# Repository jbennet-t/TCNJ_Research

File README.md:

# TCNJ_Research
Research notes, code, and PCBs created for research projects and development during my time at multiple labs. Check out the wiki for more info!

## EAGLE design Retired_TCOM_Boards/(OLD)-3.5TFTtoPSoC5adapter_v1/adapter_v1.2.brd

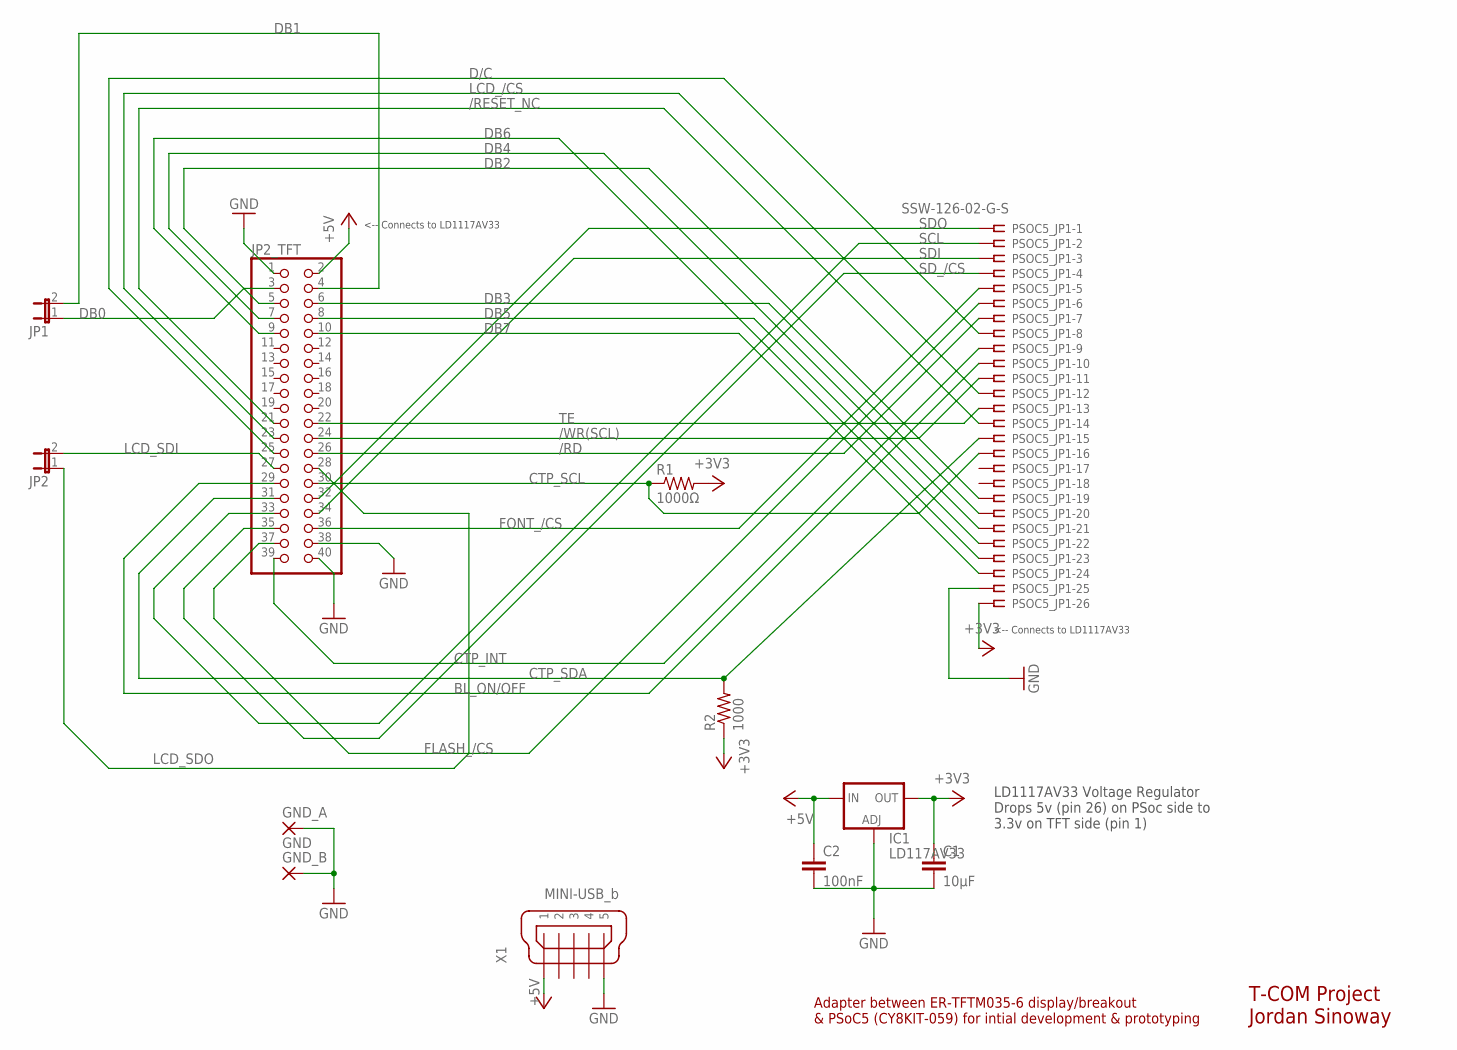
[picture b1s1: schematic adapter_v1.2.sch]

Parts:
C1: 10μF; C2.5-2
C2: 100nF; C2.5-2
GND_A: GND; SMD2,54-5,08
GND_B: SMD5; SMD2,54-5,08
IC1: LD117AV33; TO220L1
JP1, JP2: JP1E; JP1
JP2_TFT: PINHD-2X20; 2X20
PSOC5_JP1: SSW-126-02-G-S
R1: 1000Ω; 0204/7
R2: 1000; 0204/7
X1: MINI-USB_b; 32005-601

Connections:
+3V3: C1.1, IC1.2 (OUT), PSOC5_JP1.26, R1.2, R2.1
+5V: C2.1, IC1.3 (IN), JP2_TFT.2, X1.1
/RD: JP2_TFT.26, PSOC5_JP1.7
/RESET_NC: JP2_TFT.21, PSOC5_JP1.14
/WR(SCL): JP2_TFT.24, PSOC5_JP1.11
BL_ON/OFF: JP2_TFT.29, PSOC5_JP1.10
CTP_INT: JP2_TFT.39, PSOC5_JP1.9
CTP_SCL: JP2_TFT.30, PSOC5_JP1.16, R1.1
CTP_SDA: JP2_TFT.31, PSOC5_JP1.15, R2.2
D/C: JP2_TFT.25, PSOC5_JP1.8
DB0: JP1.1, JP2_TFT.3
DB1: JP1.2, JP2_TFT.4
DB2: JP2_TFT.5, PSOC5_JP1.19
DB3: JP2_TFT.6, PSOC5_JP1.20
DB4: JP2_TFT.7, PSOC5_JP1.21
DB5: JP2_TFT.8, PSOC5_JP1.22
DB6: JP2_TFT.9, PSOC5_JP1.23
DB7: JP2_TFT.10, PSOC5_JP1.24
FLASH_/CS: JP2_TFT.37, PSOC5_JP1.6
FONT_/CS: JP2_TFT.36, PSOC5_JP1.5
GND: C1.2, C2.2, GND_A.1, GND_B.1, IC1.1 (ADJ), JP2_TFT.1, JP2_TFT.38, JP2_TFT.40, PSOC5_JP1.25, X1.5
LCD_/CS: JP2_TFT.23, PSOC5_JP1.12
LCD_SDI: JP2.2, JP2_TFT.27
LCD_SDO: JP2.1, JP2_TFT.28
SCL: JP2_TFT.33, PSOC5_JP1.2
SDI: JP2_TFT.34, PSOC5_JP1.3
SDO: JP2_TFT.32, PSOC5_JP1.1
SD_/CS: JP2_TFT.35, PSOC5_JP1.4
TE: JP2_TFT.22, PSOC5_JP1.13

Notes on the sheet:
LD1117AV33 Voltage Regulator Drops 5v (pin 26) on PSoc side to 3.3v on TFT side (pin 1)
<-- Connects to LD1117AV33
T-COM Project Jordan Sinoway
Adapter between ER-TFTM035-6 display/breakout & PSoC5 (CY8KIT-059) for intial development & prototyping

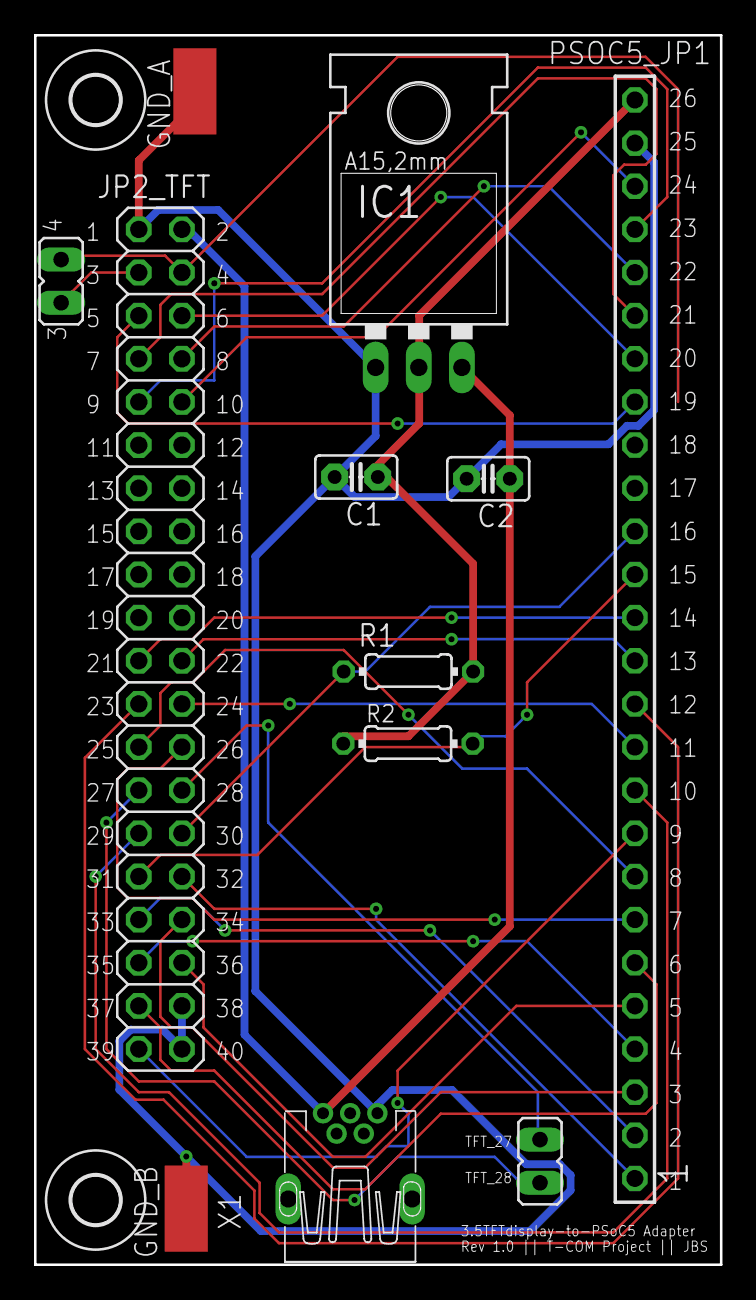
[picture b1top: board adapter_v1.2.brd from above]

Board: 2 copper layers, 40.4 x 72.4 mm, 14 parts (0 on the bottom side), 29 nets.

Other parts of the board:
U$1, U$2: 2,8

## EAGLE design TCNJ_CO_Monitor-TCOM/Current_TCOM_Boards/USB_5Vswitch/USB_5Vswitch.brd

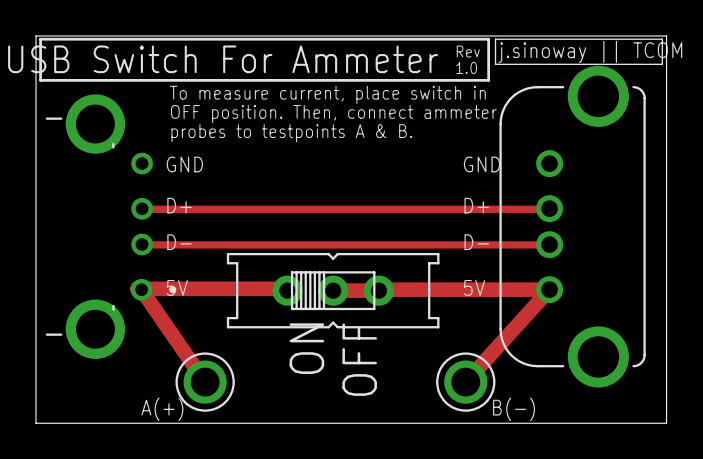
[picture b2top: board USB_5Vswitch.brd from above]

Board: 2 copper layers, 35.0 x 21.5 mm, 5 parts (0 on the bottom side), 5 nets.

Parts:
A(+): 5013; TESTPOINT_5013
B(-): 5013; TESTPOINT_5013
J1: USB-A-S-X-X-VT
J2: 1-1734028-12; TE_1-1734028-2
S1: EG1218

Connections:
+5V: B(-).1, J1.1, S1.P, S1.S
D+: J1.3, J2.3
D-: J1.2, J2.2
GND: J1.4, J1.G1, J1.G2, J2.4, J2.S1, J2.S2
unnamed: A(+).1, J2.1, S1.O

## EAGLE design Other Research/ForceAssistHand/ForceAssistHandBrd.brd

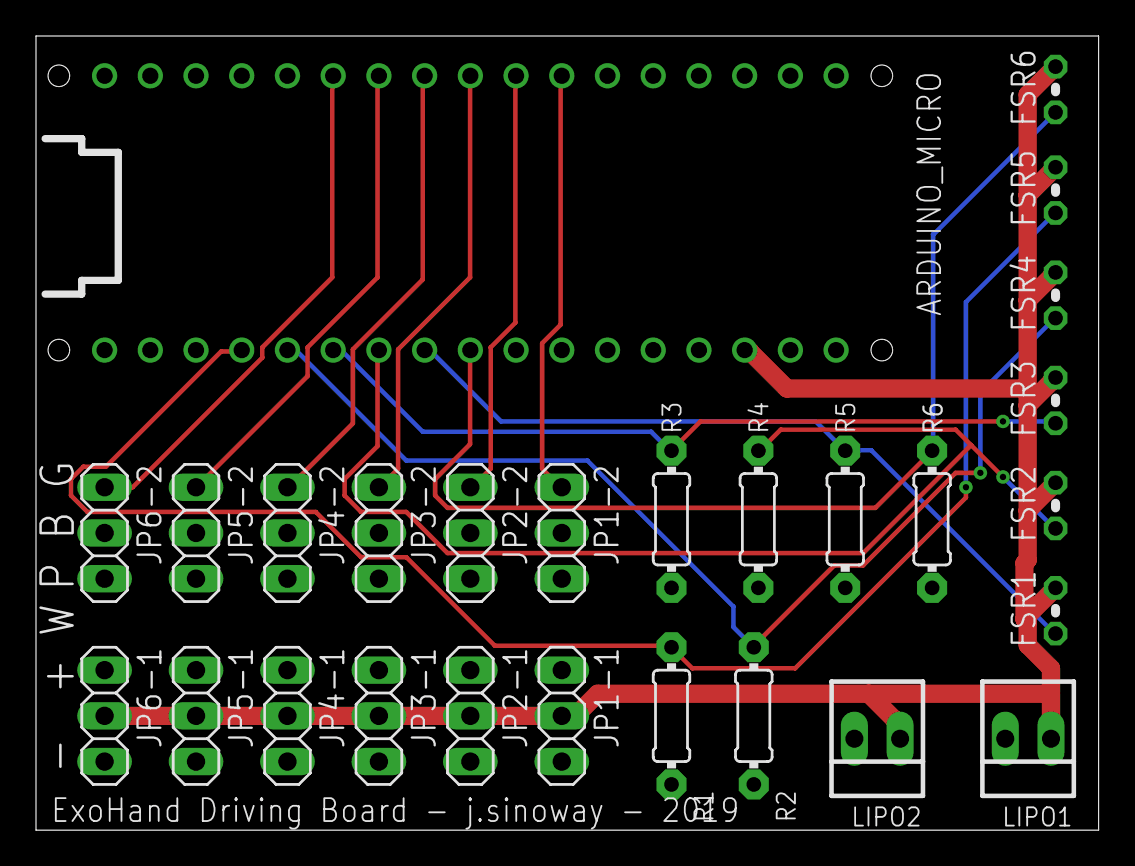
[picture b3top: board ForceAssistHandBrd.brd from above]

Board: 2 copper layers, 59.0 x 44.1 mm, 27 parts (0 on the bottom side), 14 nets.

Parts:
ARDUINO_MICRO: ARDUINO_MICROFOOTPRINT; ARDUINO-MICRO
FSR1, FSR2, FSR3, FSR4, FSR5, FSR6: 0204V
JP1-1, JP1-2, JP2-1, JP2-2, JP3-1, JP3-2, JP4-1, JP4-2, JP5-1, JP5-2, JP6-1, JP6-2: 1X03
LIPO1, LIPO2: 22-23-2021
R1, R2, R3, R4, R5, R6: 1k; 0204/7

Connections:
GND: ARDUINO_MICRO.GND, ARDUINO_MICRO.GND1, JP1-1.3, JP2-1.3, JP3-1.3, JP4-1.3, JP5-1.3, JP6-1.3, LIPO1.2, LIPO2.2, R1.2, R2.2, R3.2, R4.2, R5.2, R6.2
unnamed: ARDUINO_MICRO.D2, JP1-2.1
unnamed: ARDUINO_MICRO.D3, JP2-2.1
unnamed: ARDUINO_MICRO.D4, JP3-2.1
unnamed: ARDUINO_MICRO.D5, JP4-2.1
unnamed: ARDUINO_MICRO.D6, JP5-2.1
unnamed: ARDUINO_MICRO.A5, FSR6.1, R6.1
unnamed: ARDUINO_MICRO.A3, FSR2.1, R4.1
unnamed: ARDUINO_MICRO.A4, FSR1.1, R5.1
unnamed: ARDUINO_MICRO.A2, FSR3.1, R3.1
unnamed: ARDUINO_MICRO.A1, FSR4.1, R2.1
unnamed: ARDUINO_MICRO.A0, FSR5.1, R1.1
unnamed: ARDUINO_MICRO.D7, JP6-2.1
VCC: ARDUINO_MICRO.VIN, FSR1.2, FSR2.2, FSR3.2, FSR4.2, FSR5.2, FSR6.2, JP1-1.2, JP2-1.2, JP3-1.2, JP4-1.2, JP5-1.2, JP6-1.2, LIPO1.1, LIPO2.1

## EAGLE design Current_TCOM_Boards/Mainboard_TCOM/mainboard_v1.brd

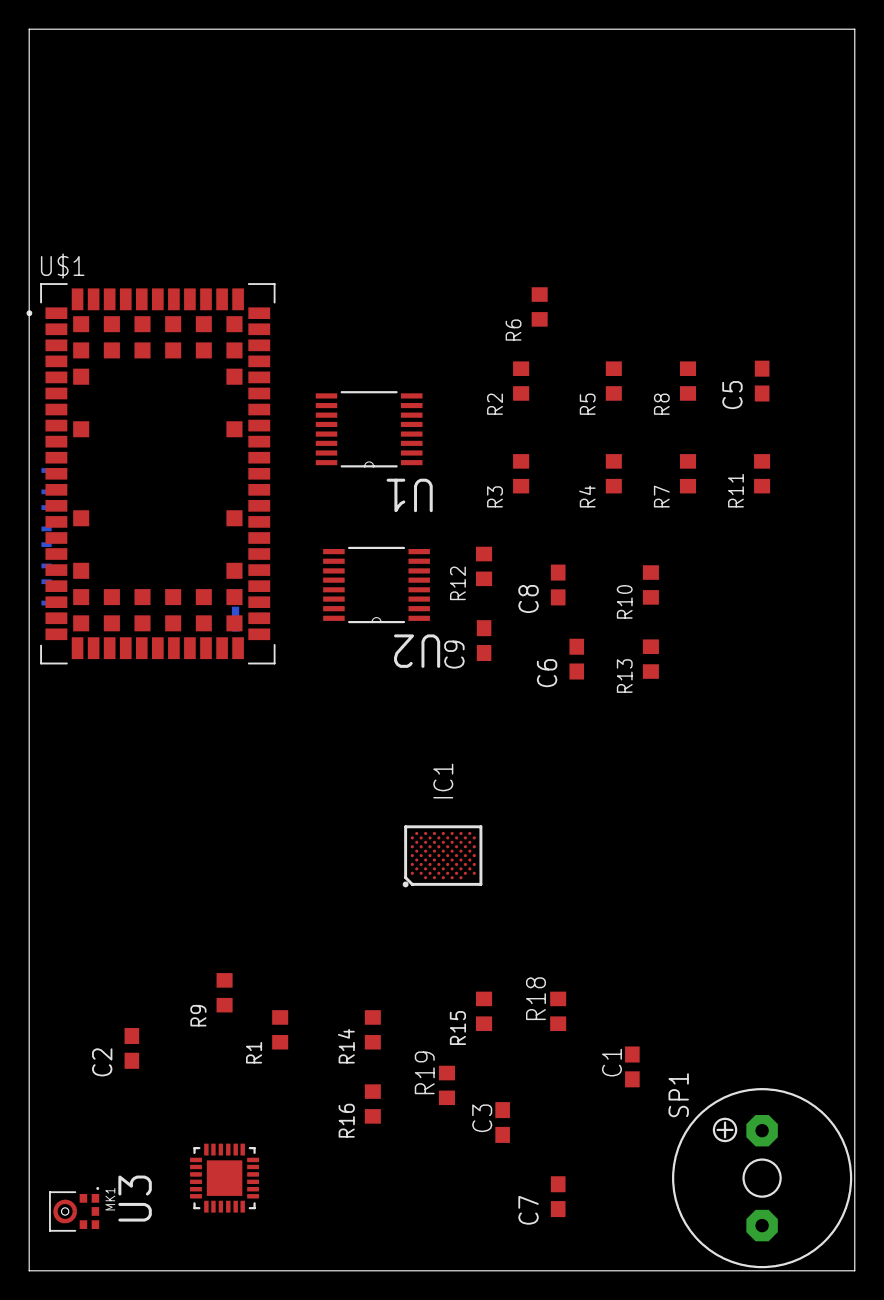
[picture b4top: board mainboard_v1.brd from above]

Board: 4 copper layers, 56.6 x 85.1 mm, 34 parts (1 on the bottom side), 30 nets, no tracks yet.

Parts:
C1: 200pF; C0603
C2, C7: 100nF; C0603
C3: .1uF; C0603
C5, C6, C8, C9: 0.01uF; C0603
IC1: CY8C6247FDI-D32T; BGA80C30P11X15_368X319X47
MK1: SPH0645LM4H-B; MIC_SPH0645LM4H-B
R1, R2, R3, R4, R5, R6, R7, R8, R9, R10, R11, R12, R13, R14, R15, R16, R18: 1k; R0603
R19: 100k; R0603
SIM: 2199337-5; TE_2199337-5
SP1: KSS1201
U1, U2: SN74AVC4T774PWR; SOP65P640X120-16N
U3: TFA9879HN/N1,118; QFN50P260X260X100-25N
U$1: SARA-U260; XCVR_SARA-N200-02B

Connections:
1.8V: C2.1, U3.23
+3V3: C1.1, C3.1, C6.1, C9.1, MK1.5, R3.2, R5.2, R11.2, U1.16, U2.16, U3.7, U3.8
ADSEL1: R15.2, U3.16
ADSEL2: R16.2, U3.4
AUDIO_SDI: MK1.6, R19.2
AUDIO_WS: MK1.1, U3.22
GND: C1.2, C2.2, C3.2, C5.2, C6.2, C7.2, C8.2, C9.2, MK1.3, R1.1, R2.2, R4.2, R6.2, R7.2, R8.2, R9.1, R10.1, R12.2, R13.2, R14.1, R15.1, R16.1, R18.1, R19.1, SIM.C5, SIM.G1, SIM.G2, SIM.G3, SIM.G4, U1.10, U2.10, U3.3, U3.5, U3.11, U3.12, U3.15, U3.24, U3.25
LRCK2: R1.2, U3.19
unnamed: R3.1, U1.1
unnamed: R4.1, U1.2
unnamed: R5.1, U1.7
unnamed: MK1.2, R18.2
unnamed: R6.1, U1.8
unnamed: R7.1, U2.1
unnamed: R11.1, U2.2
unnamed: R12.1, U2.7
unnamed: R8.1, U2.9
unnamed: R13.1, U2.8
unnamed: R10.2, U2.11
unnamed: R2.1, U1.9
SCK2: R9.2, U3.18
SDI2: R14.2, U3.17
SIM_CLK: SIM.C3, U$1.38
SIM_IO: SIM.C7, U$1.39
SIM_RST: SIM.C2, U$1.40
SP+: SP1.+, U3.10
SP-: SP1.-, U3.9
STABA: C7.1, U3.13
VSIM: SIM.C1, U$1.41
V_INT: C5.1, C8.1, U1.15, U2.15

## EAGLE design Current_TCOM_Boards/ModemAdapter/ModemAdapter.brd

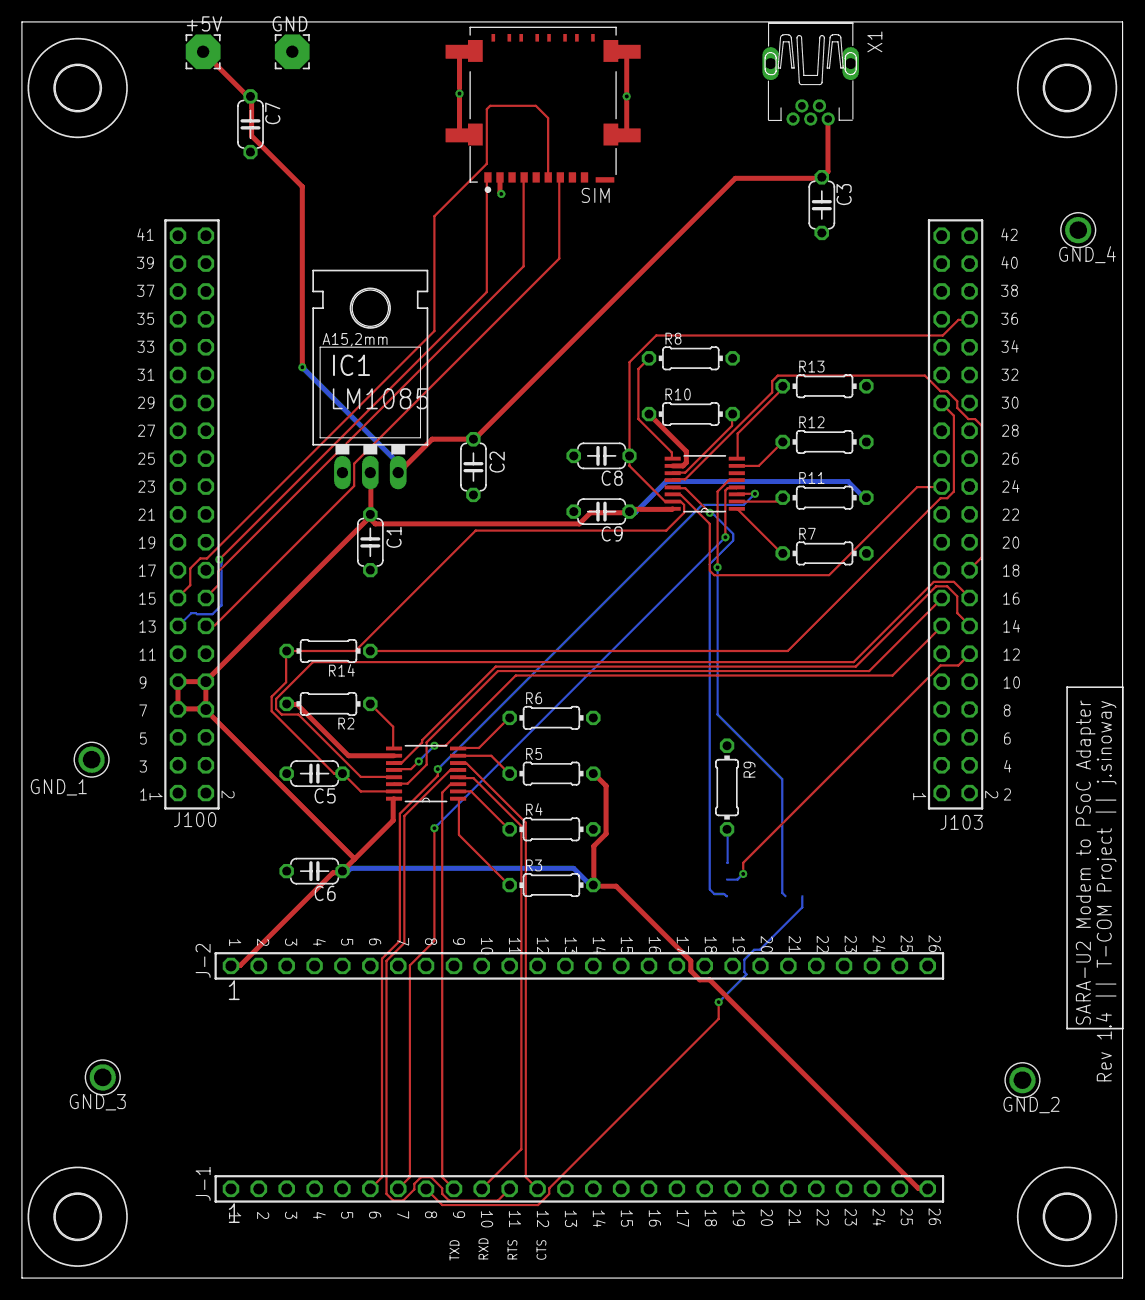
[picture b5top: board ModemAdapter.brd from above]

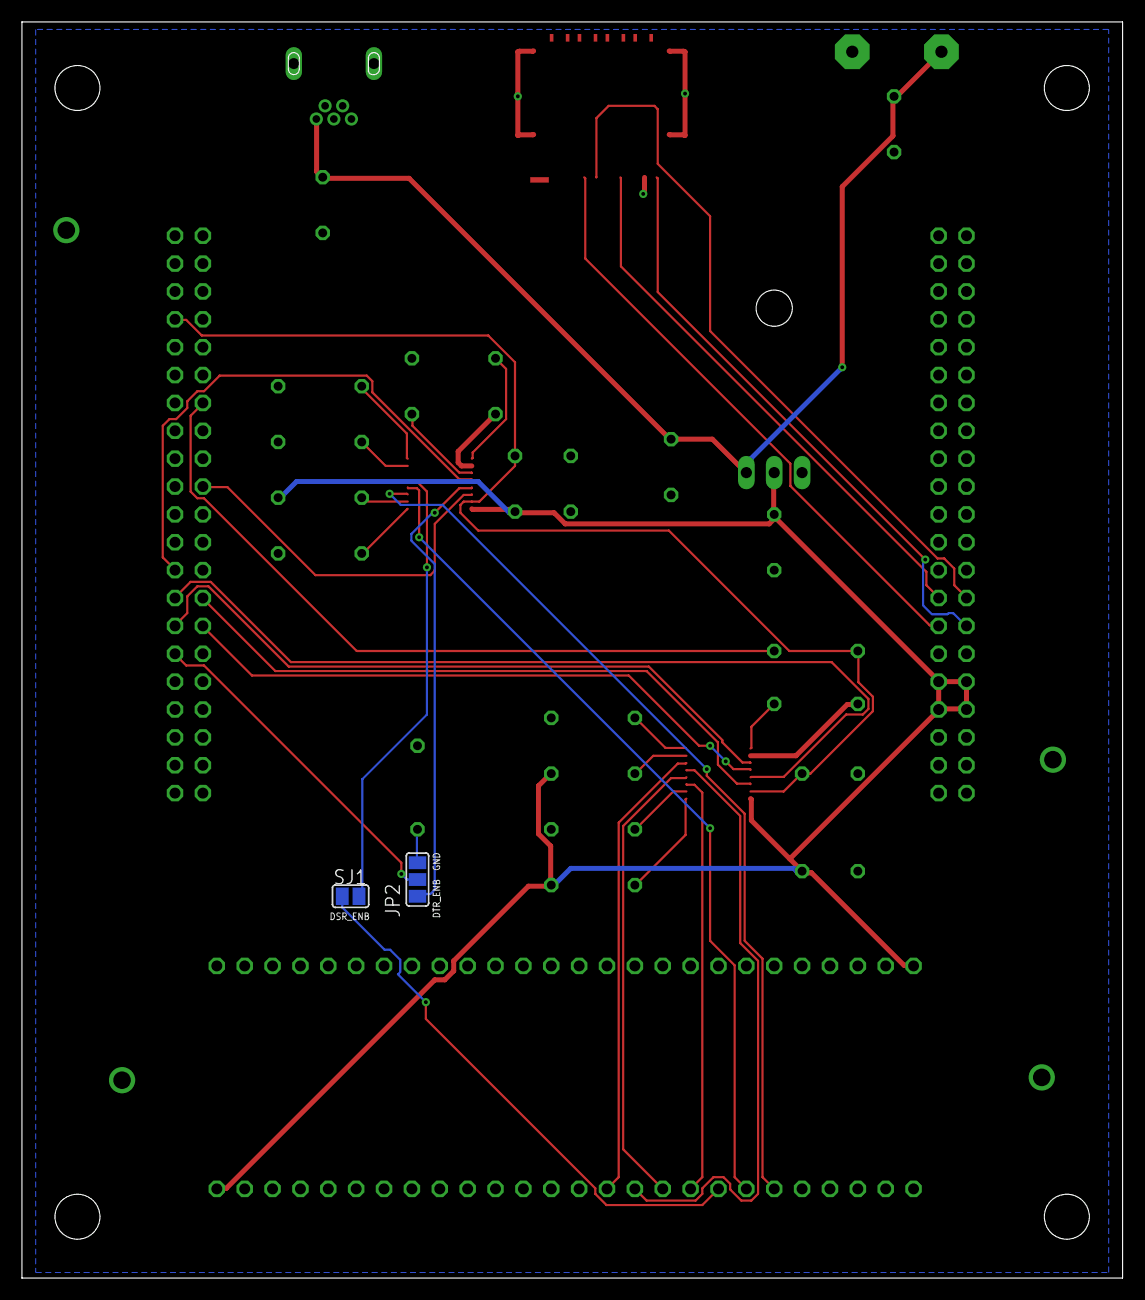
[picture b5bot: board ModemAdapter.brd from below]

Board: 2 copper layers, 100.3 x 114.5 mm, 46 parts (2 on the bottom side), 37 nets.

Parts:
+5V: 5V_IN; 3,17/1,1
C1: 10μF; C050-024X044
C2: 0.1uF; C050-024X044
C3, C7: 22uF; C050-024X044
C5, C6, C8, C9: 0.01uF; C050-024X044
GND: 3,17/1,1
GND_1, GND_2, GND_3, GND_4: 5013; TESTPOINT_5013
H1, H2, H3, H4: MOUNT-HOLE4.1; 4,1
IC1: LD117AV33; TO220L1
J100, J103: TSW-121-08-G-D; TSW-121-XX-G-D
J-1, J-2: SSW-126-02-G-S
JP2: SJ_2
PAD1, PAD2, PAD3, PAD4: SMD1,27-2,54
R2, R3, R4, R5, R6, R7, R8, R9, R10, R11, R12, R13, R14: 1k; 0204/7
SIM: 2199337-5; TE_2199337-5
SJ1: SJ
U1, U2: SN74AVC4T774PWR; SOP65P640X120-16N
X1: MINI-USB_b; 32005-601

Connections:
+3V3: C1.1, C6.1, C9.1, IC1.2, J100.7, J100.8, J100.9, J100.10, J-1.26, J-2.1, R3.2, R5.2, R11.2, U1.16, U2.16
+5V: +5V.1, C2.1, C3.1, C7.1, IC1.3, X1.1
CTS_A: J-1.12, U1.6
CTS_B: J103.14, U1.11
DSR_A1: J-1.8, SJ1.1
DSR_A2: SJ1.2, U2.5
DSR_B: J103.18, U2.12
DTR_A: J-1.7, U2.4
DTR_B1: J103.12, JP2.2
DTR_B2: JP2.1, U2.13
GND: C1.2, C2.2, C3.2, C5.2, C6.2, C7.2, C8.2, C9.2, GND.1, GND_1.1, GND_2.1, GND_3.1, GND_4.1, IC1.1, J103.7, J103.8, J103.9, J103.10, J-1.25, J-2.2, J-2.26, PAD1.1, PAD2.1, PAD3.1, PAD4.1, R2.2, R4.2, R6.2, R7.2, R8.2, R9.1, R10.1, R12.2, R13.2, SIM.C5, SIM.G1, SIM.G2, SIM.G3, SIM.G4, U1.10, U2.10, X1.5
unnamed: R3.1, U1.1
unnamed: R4.1, U1.2
unnamed: R5.1, U1.7
unnamed: R6.1, U1.8
unnamed: R7.1, U2.1
unnamed: R11.1, U2.2
unnamed: R12.1, U2.7
unnamed: R8.1, U2.9
unnamed: JP2.3, R9.2
unnamed: R13.1, U2.8
unnamed: R10.2, U2.11
unnamed: R2.1, U1.9
PWR_ON: J103.29, R14.1
RTS_A: J-1.11, U1.5
RTS_B: J103.13, U1.12
RXD_A: J-1.10, U1.4
RXD_B: J103.16, U1.13
SIM_CLK: J100.15, SIM.C3
SIM_DET_A: J-1.6, U2.3
SIM_DET_B: J103.23, U2.14
SIM_IO: J100.14, SIM.C7
SIM_RST: J100.16, SIM.C2
TXD_A: J-1.9, U1.3
TXD_B: J103.15, U1.14
VSIM: J100.13, SIM.C1
V_INT: C5.1, C8.1, J103.36, R14.2, U1.15, U2.15

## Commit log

2019-09-01 First commit of all research PCBs
2019-10-08 fixing file structure
2019-10-08 added robotics research files, adjusted directory layout
2019-10-25 added pdf schematics of parts, before transition to Solidworks
2019-10-25 updated pdf schematic of elbow fork before transition to solidworks
2020-01-18 added c microcontroller benchmarks for psoc and arduino
2020-01-18 added comments to arduino files
2020-01-24 adding simple robot arm PCBs
2020-01-24 added PSoC code for Simple robot arm
